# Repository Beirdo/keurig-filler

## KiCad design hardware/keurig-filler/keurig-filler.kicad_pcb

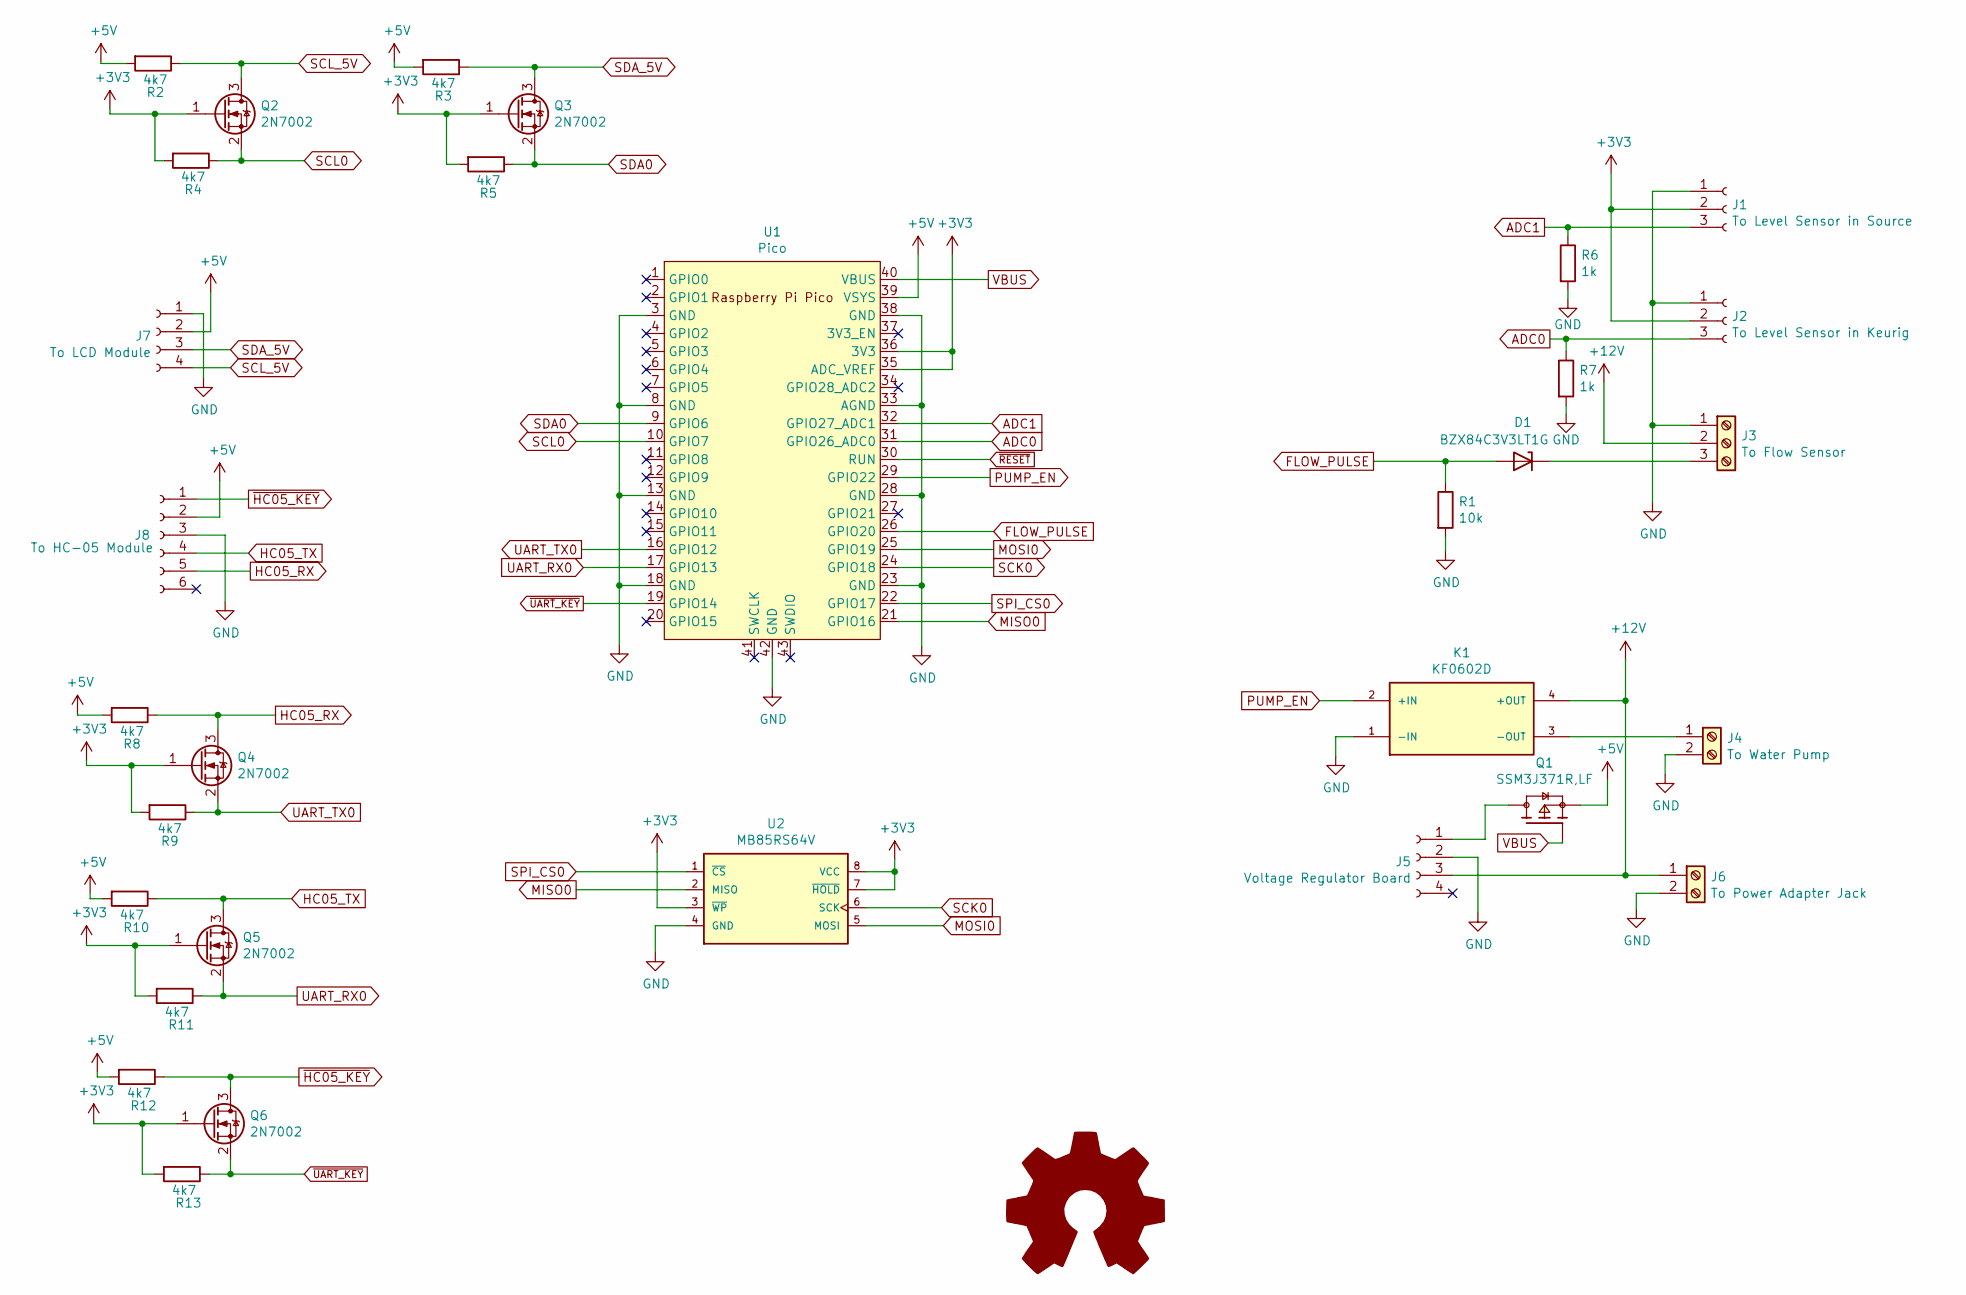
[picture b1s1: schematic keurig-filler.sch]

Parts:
D1: BZX84C3V3LT1G; D_SOT-23_ANK
J1: To Level Sensor in Source; PinHeader_1x03_P2.54mm_Vertical
J2: To Level Sensor in Keurig; PinHeader_1x03_P2.54mm_Vertical
J3: To Flow Sensor; TerminalBlock_Altech_AK300-3_P5.00mm
J4: To Water Pump; TerminalBlock_Altech_AK300-2_P5.00mm
J5: Voltage Regulator Board; PinHeader_1x04_P2.54mm_Vertical
J6: To Power Adapter Jack; TerminalBlock_Altech_AK300-2_P5.00mm
J7: To LCD Module; PinHeader_1x04_P2.54mm_Vertical
J8: To HC-05 Module; PinHeader_1x06_P2.54mm_Vertical
K1: KF0602D; RELAY_KF0602D; PARTREV N/A
Q1: ‎SSM3J371R,LF‎; SOT91P240X110-3N_DMG2305UX-7; PARTREV 09/2018
Q2, Q3, Q4, Q5, Q6: 2N7002; SOT-23
R1: 10k; R_0805_2012Metric_Pad1.20x1.40mm_HandSolder
R2, R3, R4, R5, R8, R9, R10, R11, R12, R13: 4k7; R_0805_2012Metric_Pad1.20x1.40mm_HandSolder
R6, R7: 1k; R_0805_2012Metric_Pad1.20x1.40mm_HandSolder
U1: Pico; RPi_Pico_SMD_TH
U2: MB85RS64V; SOIC127P600X155-8_R159_68_374R15

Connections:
+3V3: J1.2, J2.2, Q2.1 (G), Q3.1 (G), Q4.1 (G), Q5.1 (G), Q6.1 (G), R4.2, R5.2, R9.2, R11.2, R13.2, U1.35 (ADC_VREF), U1.36 (3V3), U2.3 (~WP), U2.7 (~HOLD), U2.8 (VCC)
+5V: J7.2, J8.2, Q1.2, R2.2, R3.2, R8.2, R10.2, R12.2, U1.39 (VSYS)
+12V: J3.2, J5.3, J6.1, K1.4 (+OUT)
ADC0: J2.3, R7.1, U1.31 (GPIO26_ADC0)
ADC1: J1.3, R6.1, U1.32 (GPIO27_ADC1)
FLOW_PULSE: D1.2 (A), R1.1, U1.26 (GPIO20)
GND: J1.1, J2.1, J3.1, J4.2, J5.2, J6.2, J7.1, J8.3, K1.1 (-IN), R1.2, R6.2, R7.2, U1.3 (GND), U1.8 (GND), U1.13 (GND), U1.18 (GND), U1.23 (GND), U1.28 (GND), U1.33 (AGND), U1.38 (GND), U1.42 (GND), U2.4 (GND)
HC05_RX: J8.5, Q4.3 (D), R8.1
HC05_TX: J8.4, Q5.3 (D), R10.1
MISO0: U1.21 (GPIO16), U2.2 (MISO)
MOSI0: U1.25 (GPIO19), U2.5 (MOSI)
unnamed: D1.1 (K), J3.3
unnamed: J4.1, K1.3 (-OUT)
unnamed: J5.1, Q1.3
PUMP_EN: K1.2 (+IN), U1.29 (GPIO22)
SCK0: U1.24 (GPIO18), U2.6 (SCK)
SCL0: Q2.2 (S), R4.1, U1.10 (GPIO7)
SCL_5V: J7.4, Q2.3 (D), R2.1
SDA0: Q3.2 (S), R5.1, U1.9 (GPIO6)
SDA_5V: J7.3, Q3.3 (D), R3.1
SPI_CS0: U1.22 (GPIO17), U2.1 (~CS)
UART_RX0: Q5.2 (S), R11.1, U1.17 (GPIO13)
UART_TX0: Q4.2 (S), R9.1, U1.16 (GPIO12)
VBUS: Q1.1, U1.40 (VBUS)
~HC05_KEY: J8.1, Q6.3 (D), R12.1
~RESET: U1.30 (RUN)
~UART_KEY: Q6.2 (S), R13.1, U1.19 (GPIO14)

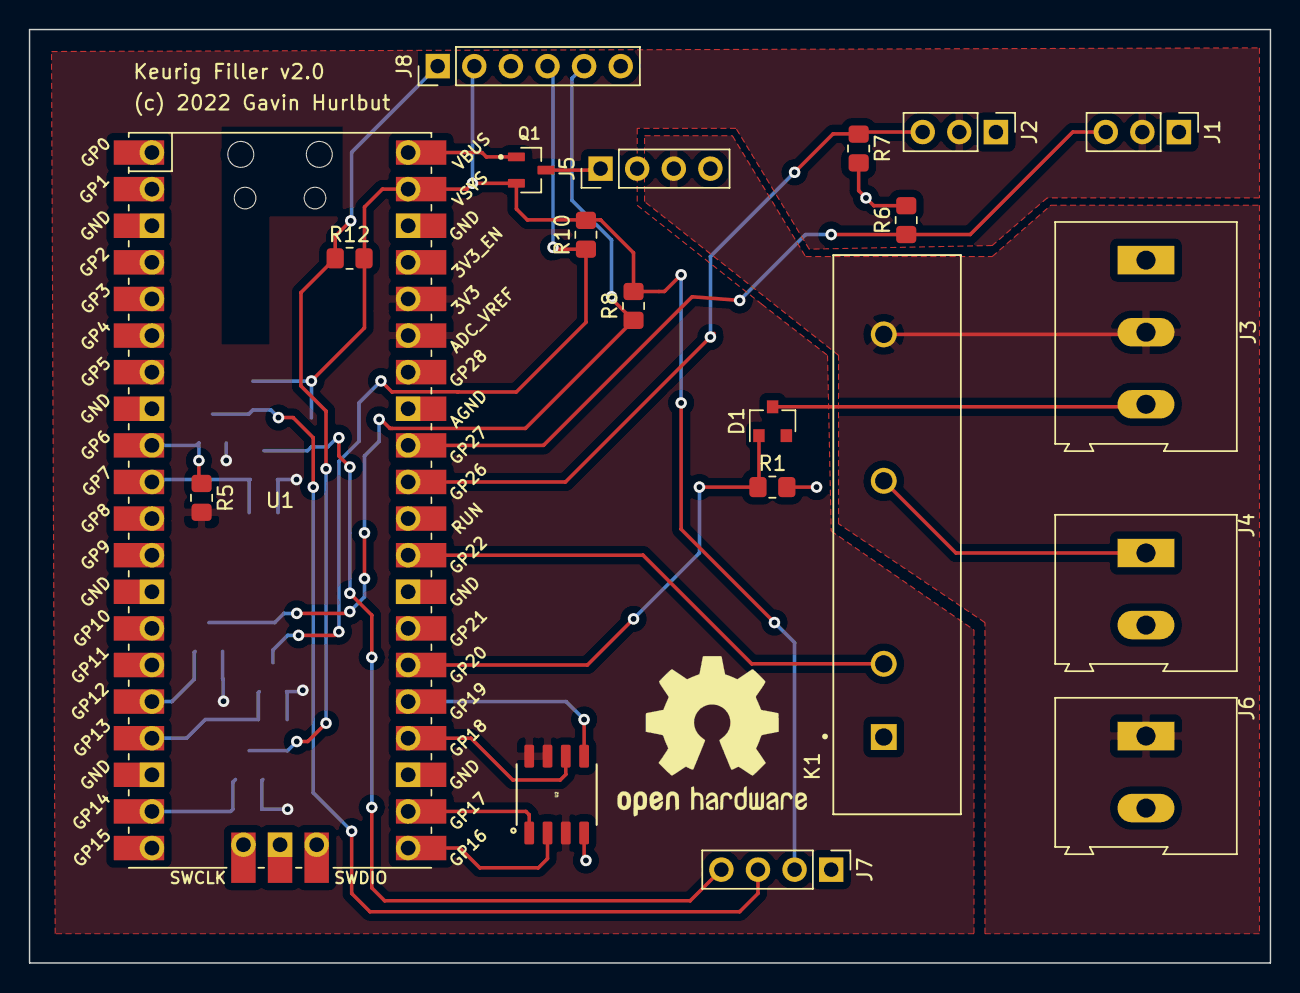
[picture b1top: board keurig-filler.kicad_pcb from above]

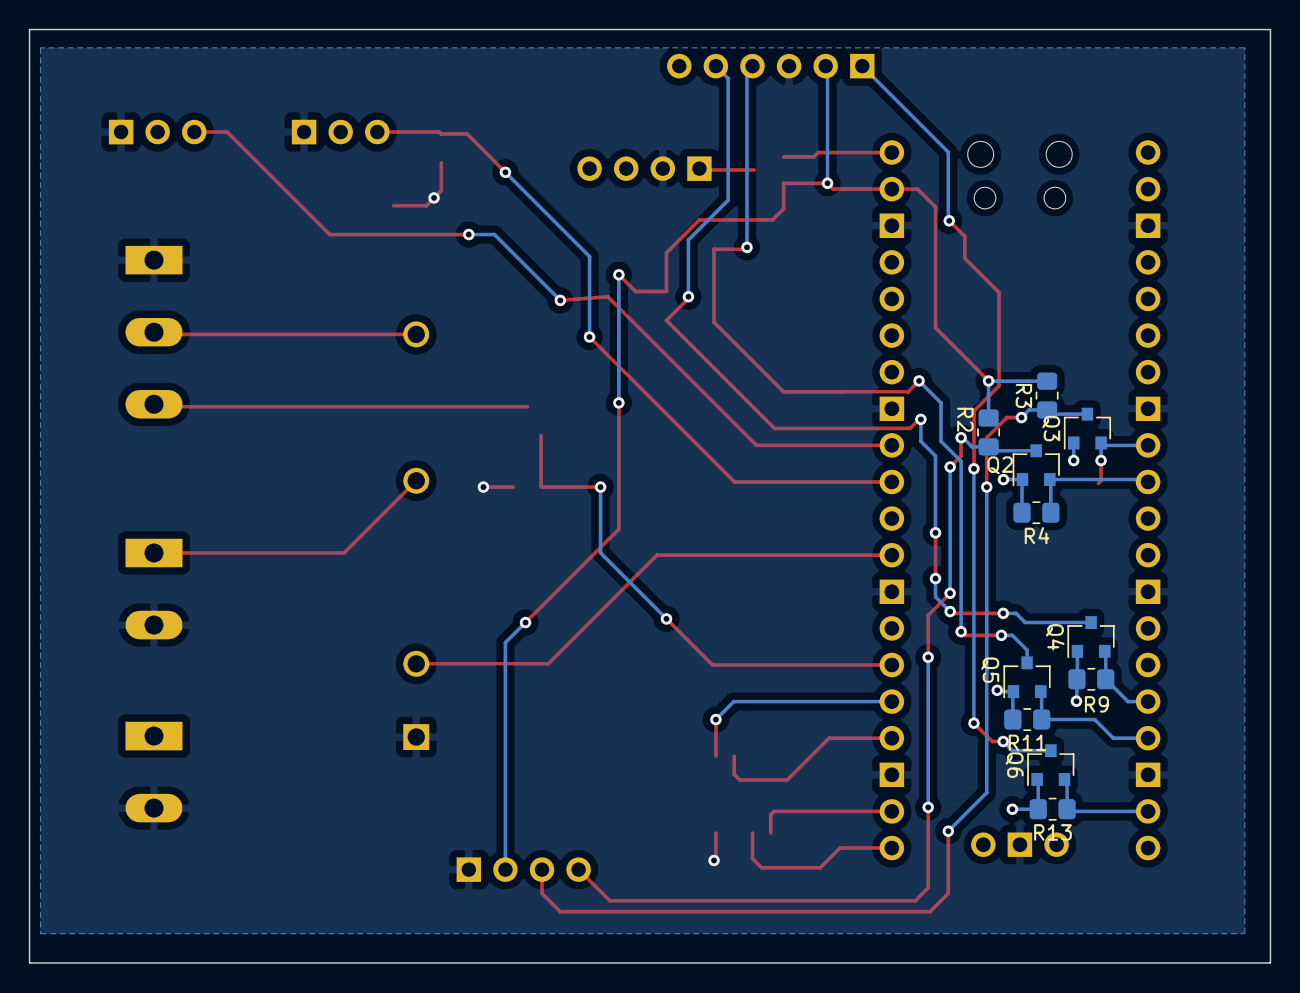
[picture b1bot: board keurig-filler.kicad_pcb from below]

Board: 2 copper layers, 86.1 x 64.8 mm, 31 parts (11 on the bottom side), 26 nets.

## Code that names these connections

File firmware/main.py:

import _thread
import math
import os
import time

from machine import Pin, ADC, SPI, I2C, UART, Signal

from eeprom.fram.fram_spi import FRAM
from fram_data import FRAMSettings
from lcd_handler import LCDHandler
from pump_states import StateMachine, PumpStates
from utils import _log, add_log_file

"""
This will be primarily interrupt-driven, and timer driven.
Basic Flow:
    1) Setup the I/Os and IRQ handler
    2) Start a timer to do ADC readings for both level sensors every second
    3) On interrupt from the flow sensor, increment a counter, which we reset every second in the timer handler

Timer Handler:
    1) Read ADC0 to get a level reading at the Keurig's reservoir
    2) Read ADC1 to get a level reading at the 5gal source jug
    3) Read out the flow counter and reset to zero
    4) Update pump control state-machine
    5) Send update out UART (over USB)
"""

scale_a = math.log(2.053)
scale_b = math.log(0.9989)


def scale_liquid_level(value):
    _log("%03X" % value)

    '''
    First we need to calculate the resistance, much like one would with a
    thermistor.   We create a resistive voltage divider with a resistor going
    from the ADC input to ground.  I have chosen a 1k resistor as it seemed to
    be relatively similar to much of the range.
    
    In the end the resistance vs level graph is an exponential decay that looks
    very much like the ones for NTD thermistors
    '''
    r = 1000
    vin = 3.3
    vo = 3.3 * value / 4096
    r_sensor = r * ((vin / vo) - 1)
    _log("%0.3f ohm" % r_sensor)

    '''
    Now, let's calibrate this (using empirically determined values).  At 100% we
    see around 700 ohms, and at 1% (just starting to trigger) it's around 4k ohms.
    When the sensor is completely dry, it gets to around 100k ohms.  We'll cap the
    measured value
    '''
    sensor_min_r = 700
    sensor_max_r = 4000
    sensor_r_range = sensor_max_r - sensor_min_r

    r_sensor = min(sensor_max_r, max(sensor_min_r, r_sensor))
    _log("%0.3f ohm" % r_sensor)

    '''
    We are going to use exponential regression (two layers deep) to find
    the % full based on:
        x       y = R
        0       4000
        25      1150
        50      800
        75      720
        100     700
        
    After the first logarithm:
        x        y1 = ln(y)
        0        8.294049
        25       7.047517
        50       6.684612
        75       6.579251
        100      6.55108
        
    This is still clearly somewhat exponential.
    
    After the second logarithm:
        x        y2 = ln(y1)
        0        2.115538
        25       1.952675
        50       1.899808
        75       1.883921
        100      1.87963
        
    This maps out to:
       y2 = a * b^x
       with a = 2.053, b = 0.9989
         
       y2 = 2.053 * 0.9989^x
    
        x = (ln(y2) - ln(a)) / ln(b)
    '''

    y1 = math.log(r_sensor)
    y2 = math.log(y1)
    y3 = math.log(y2)
    percent_value = max(0.0, (y3 - scale_a) / scale_b)
    _log("Scaled %%: %0.3f" % percent_value)
    return percent_value


def pulse_irq(pin):
    global flow_count
    with flow_mutex:
        flow_count += 1


keurig_level = 0.0
source_level = 0.0
pump_on_seconds = 0.0
liters_pumped = 0.0

display_vars = {
    "keurig_level": 0.0,
    "source_level": 0.0,
    "liters_pumped": 0,
    "pump_on_seconds": 0,
}

display_items = [
    {
        "x": 0,
        "y": 0,
        "static": "Keurig:",
    },
    {
        "x": 7,
        "y": 0,
        "format": "%03.1%%",
        "variable": "keurig_level",
        "clear_to_eol": True,
    },
    {
        "x": 0,
        "y": 1,
        "static": "Source:",
    },
    {
        "x": 7,
        "y": 1,
        "format": "%03.1%%",
        "variable": "source_level",
        "clear_to_eol": True,
    },
    {
        "x": 0,
        "y": 2,
        "static": "Pumped:",
    },
    {
        "x": 7,
        "y": 2,
        "format": "%12dL",
        "variable": "liters_pumped",
        "clear_to_eol": True,
    },
    {
        "x": 0,
        "y": 3,
        "static": "Time:",
    },
    {
        "x": 7,
        "y": 4,
        "format": "%12ds",
        "variable": "pump_on_seconds",
        "clear_to_eol": True,
    },
]


def update_lcd_display(lcd: LCDHandler):
    for item in display_items:
        if "static" in item:
            str_ = item.get("static", "")
        else:
            value = display_vars.get(item.get("variable", None), 0)
            str_ = item.get("format", "") % value
        lcd.put_str(str_, item.get("x", -1), item.get("y", -1), item.get("clear_to_eol", False))
    lcd.refresh()


flow_mutex = _thread.allocate_lock()

v2_detect = Pin(28, Pin.IN, Pin.PULL_UP).value()
if not v2_detect:
    version = 1
    fram_settings = None
    lcd = None
else:
    # Hookup the HC-05 on UART0
    uart_key_pin = Pin(14, Pin.OPEN_DRAIN, value=1)
    uart_key = Signal(uart_key_pin, invert=True)
    uart_key.off()

    uart = UART(0, baudrate=115200, rx=Pin(13), tx=Pin(12))
    add_log_file(uart)

    # Hook up the FRAM on SPI0
    supported_version = 2
    spi = SPI(0, baudrate=25_000_000, polarity=0, phase=0, sck=Pin(18), mosi=Pin(19), miso=Pin(16))
    spi_cs0 = Pin(17, Pin.OUT, value=1)
    fram = FRAM(spi, [spi_cs0], size=64)
    # Only need to run this once!
    # os.VfsLfs2.mkfs(fram)
    os.mount(fram, "/fram")
    fram_settings = FRAMSettings("/fram/settings.cbor", supported_version)

    version = fram_settings.get("version", supported_version)
    liters_pumped = fram_settings.get("liters_pumped", 0.0)
    pump_on_seconds = fram_settings.get("pump_on_seconds", 0.0)

    # Hook up the LCD on I2C0
    i2c = I2C(0, scl=Pin(7), sda=Pin(6))
    # Only need to run this once to get the right addr
    # i2c.scan()
    lcd = LCDHandler(i2c, 0x27)

pump_pin = Pin(22, Pin.OUT, value=0)
pump_en = Signal(pump_pin, invert=False)

flow_count = 0

flow_pulse = Pin(20, Pin.IN, Pin.PULL_DOWN)
flow_pulse.irq(pulse_irq, Pin.IRQ_RISING)

flow_factor = 1.0 / 740

pump_state = StateMachine()
loop_counter = 0

total_flow = 0.0
instance_flow = 0.0

while True:
    with flow_mutex:
        counter = flow_count
        flow_count = 0

    flow = counter * flow_factor
    instance_flow += flow
    if version >= 2:
        liters_pumped += flow
        fram_settings.set("liters_pumped", liters_pumped)

    loop_counter += 1

    '''
    MicroPython has some stupid method of expanding to 16 bit values which is not linear.  We will use the
    original 12bit ADC readings, thanks.  Also, since these sensors are finnicky, average over 8 values.
    '''
    keurig_levels = [ADC(0).read_u16() for i in range(8)]
    _log("Keurig: %s" % list(map(lambda x: "%04X" % x, keurig_levels)))
    keurig_level = scale_liquid_level(sum(keurig_levels) >> 7)

    source_levels = [ADC(1).read_u16() for i in range(8)]
    _log("Source: %s" % list(map(lambda x: "%04X" % x, source_levels)))
    source_level = scale_liquid_level(sum(source_levels) >> 7)

    if pump_state.state == PumpStates().PUMP and flow == 0.0:
        # The pump is on, but no water flowing?!  Shut it off!
        pump_state.transition(PumpStates().STOP)
    elif source_level < 10.0:
        # We are almost out of water.  Stop pumping if we are, and don't start until there's water
        pump_state.transition(PumpStates().NO_WATER)
    elif keurig_level < 5.0:
        # We have source water, and the Keurig is low on water.  Start pumping!
        pump_state.transition(PumpStates().PUMP)
    elif keurig_level > 75.0:
        # The Keurig is getting full enough, we can stop now.
        pump_state.transition(PumpStates().STOP)

    on_time = pump_state.get_on_time()
    if on_time:
        _log("Water pumped: %0.3fL" % instance_flow)
        instance_flow = 0.0

        if version >= 2:
            pump_on_seconds += on_time
            fram_settings.set("pump_on_seconds", pump_on_seconds)

    _log("%s: State: %s, Keurig Level: %0.2f, Source Level %0.2f, Flow: %0.3f" %
         (loop_counter, PumpStates(value=pump_state.state).name, keurig_level, source_level, flow))

    if version >= 2:
        display_vars.update({
            "keurig_level": keurig_level,
            "source_level": source_level,
            "liters_pumped": int(liters_pumped),
            "pump_on_seconds": int(pump_on_seconds),
        })
        update_lcd_display(lcd)
        fram_settings.write()

    time.sleep(1.0)

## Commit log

2022-01-15 Initial KiCad setup
2022-01-16 Added Kicad schematic and layout for v1
2022-01-16 Add schematic in PDF
2022-01-17 Add initial attempt at MicroPython Firmware
    Note: I don't have the board yet, can't test it.
2022-01-17 Haha, forgot the 1s sleep at the end of the main loop
2022-01-17 Use 12bit ADC readings, not the funky upscaling
2022-01-22 Complete overhaul of water sensor code
    - now doing 8 measurements, and averaging the results before conversion
    - conversion now calculates the resistance (much like with a thermistor), and then uses exponential regression to get the percentage of fullscale reading.
2022-01-22 Created v2 board design
    Adding HC-05 bluetooth module, LCD screen (over I2C) and a FRAM (over SPI). Full firmware support for the FRAM and LCD not yet added.
    Gerbers not yet regenerated.
2022-01-22 Added submodules for LCD and for eeprom/fram
2022-01-22 Fixed typo on path for eeprom lib
2022-01-23 Fleshed out LCD and FRAM use for v2 boards
    Decided to use littlefs on the FRAM, and store the parameters in CBOR format.
2022-01-23 Use Signal() where appropriate
2022-01-23 Actually write out to FRAM
2022-01-23 Updated submodules to include __init__ files
2022-01-23 Update gerbers for v2
2022-01-23 Moved the hardware directory up one.
2022-01-23 Add the gerbers.zip file to the ignores

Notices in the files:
hardware/keurig-filler/keurig-filler.kicad_pcb:
(c) 2022 Gavin Hurlbut
